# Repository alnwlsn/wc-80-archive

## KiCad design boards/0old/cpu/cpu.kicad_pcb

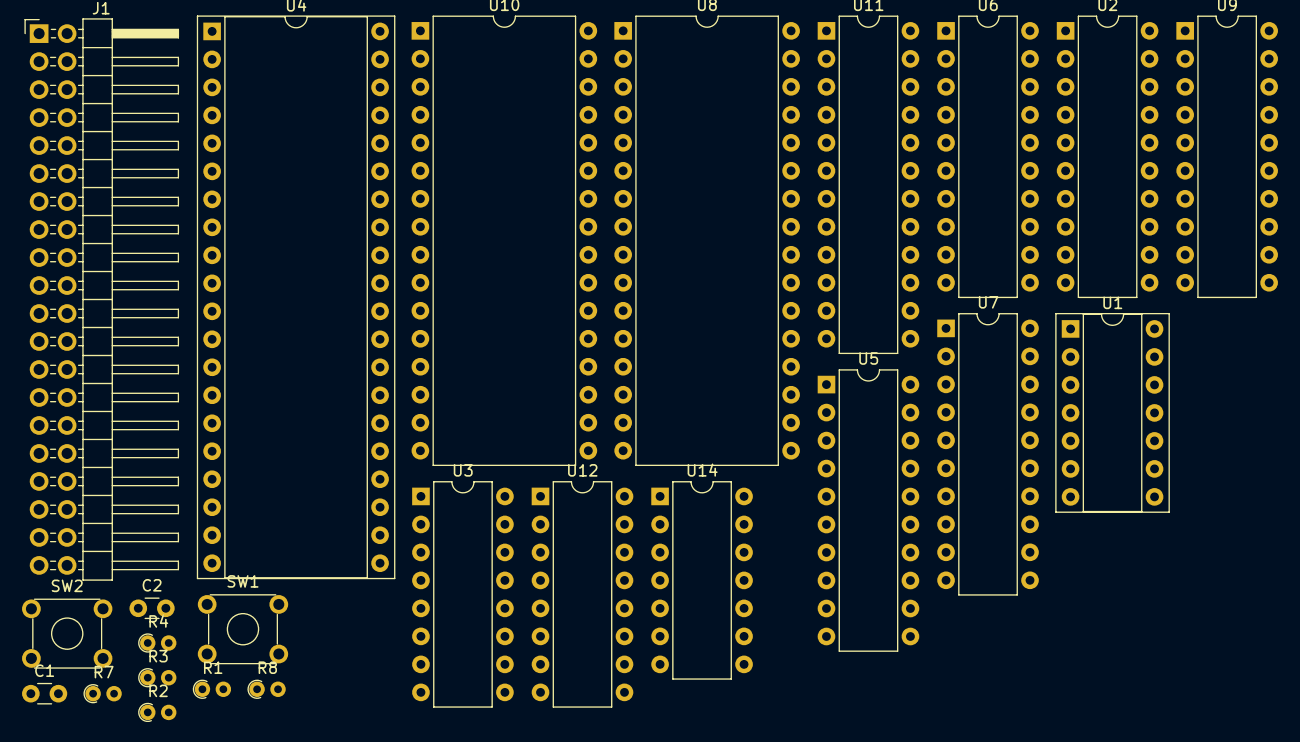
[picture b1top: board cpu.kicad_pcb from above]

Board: 2 copper layers, 24 parts (0 on the bottom side), 87 nets, no tracks yet.

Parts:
C1, C2: 1uF; C_Disc_D3.0mm_W1.6mm_P2.50mm
J1: Z80-BUS; PinHeader_2x20_P2.54mm_Horizontal
R1, R3: 100; R_Axial_DIN0204_L3.6mm_D1.6mm_P1.90mm_Vertical
R2, R4: 4k7; R_Axial_DIN0204_L3.6mm_D1.6mm_P1.90mm_Vertical
R7, R8: 330; R_Axial_DIN0204_L3.6mm_D1.6mm_P1.90mm_Vertical
SW1: RESET; SW_TH_Tactile_Omron_B3F-10xx
SW2: NMI; SW_TH_Tactile_Omron_B3F-10xx
U1: SN74HCT32N; DIP-14_W7.62mm_Socket
U2: SN74HCT244N; DIP-20_W7.62mm
U3, U12: 74LS670N; DIP-16_W7.62mm
U4: Z80CPU; DIP-40_W15.24mm_Socket
U5, U6: SN74HCT32N; DIP-20_W7.62mm
U7: 74HCT245N; DIP-20_W7.62mm
U8: 628128_DIP32_SSOP32; DIP-32_W15.24mm
U9: 74HCT273; DIP-20_W7.62mm
U10: SST39SF040; DIP-32_W15.24mm
U11: GAL22V10; DIP-24_W7.62mm
U14: 74LS132N; DIP-14_W7.62mm

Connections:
*CPUMEM: J1.10, U9.19
*EXTMEM: J1.9, U11.13
+5V: J1.1, J1.3, R2.2, R4.2, U1.14, U2.20, U4.11, U5.20, U6.20, U7.20, U8.30, U8.32, U9.20, U10.31, U10.32, U11.24
/ramAltHigh: U9.16, U11.15
/ramAltLow: U9.15, U11.16
/~rom~ram: U9.12, U11.14
BIOL: U9.11, U11.23
GND: C1.2, C2.2, J1.2, J1.4, SW1.1, SW2.1, U1.7, U2.10, U2.19, U4.29, U5.10, U6.10, U7.10, U8.16, U9.10, U10.16, U11.12
unnamed: C1.1, R1.1, R2.1, U14.1, U14.2
unnamed: C2.1, R3.1, R4.1, U14.4, U14.5
unnamed: R1.2, SW1.2
unnamed: R3.2, SW2.2
unnamed: R7.2, U14.3
unnamed: R8.2, U14.6
unnamed: U1.1, U1.13, U4.19
unnamed: U1.2, U1.5, U4.21, U7.1
unnamed: U1.3, U2.2
unnamed: U1.4, U1.9, U4.20
unnamed: U1.6, U2.6
unnamed: U1.8, U2.8
unnamed: U1.10, U1.12, U4.22
unnamed: U1.11, U2.4
unnamed: U2.1, U5.1, U5.19, U6.1, U6.19, U7.19
unnamed: U2.7, U4.24
unnamed: U2.9, U4.16
unnamed: U4.1, U6.8
unnamed: U4.2, U6.11
unnamed: U4.3, U6.13
unnamed: U4.4, U6.15
unnamed: U4.5, U6.17
unnamed: U4.7, U7.6
unnamed: U4.8, U7.5
unnamed: U4.9, U7.7
unnamed: U4.10, U7.8
unnamed: U4.12, U7.4
unnamed: U4.13, U7.9
unnamed: U4.14, U7.2
unnamed: U4.15, U7.3
unnamed: U4.30, U5.2
unnamed: U4.31, U5.4
unnamed: U4.32, U5.6
unnamed: U4.33, U5.8
unnamed: U4.34, U5.11
unnamed: U4.35, U5.13
unnamed: U4.36, U5.15
unnamed: U4.37, U5.17
unnamed: U4.38, U6.2
unnamed: U4.39, U6.4
unnamed: U4.40, U6.6
unnamed: U9.9, U10.1
unnamed: U9.5, U10.2
unnamed: U9.2, U10.3
unnamed: U9.6, U10.30
RAMA15: U8.31, U11.18
RAMA16: U8.2, U11.19
ZA0: J1.19, U8.12, U10.12, U11.9
ZA1: J1.20, U8.11, U10.11, U11.8
ZA2: J1.21, U8.10, U10.10, U11.7
ZA3: J1.22, U8.9, U10.9, U11.6
ZA4: J1.23, U8.8, U10.8, U11.5
ZA5: J1.24, U8.7, U10.7, U11.4
ZA6: J1.25, U8.6, U10.6, U11.3
ZA7: J1.26, U8.5, U10.5, U11.2
ZA8: J1.27, U8.27, U10.27
ZA9: J1.28, U8.26, U10.26
ZA10: J1.29, U8.23, U10.23
ZA11: J1.30, U8.25, U10.25
ZA12: J1.31, U8.4, U10.4
ZA13: J1.32, U8.28, U10.28
ZA14: J1.33, U8.3, U10.29
ZA15: J1.34, U11.17
ZD0: J1.11, U8.13, U9.3, U10.13
ZD1: J1.12, U8.14, U9.4, U10.14
ZD2: J1.13, U8.15, U9.7, U10.15
ZD3: J1.14, U8.17, U9.8, U10.17
ZD4: J1.15, U8.18, U9.13, U10.18
ZD5: J1.16, U8.19, U9.14, U10.19
ZD6: J1.17, U8.20, U9.17, U10.20
ZD7: J1.18, U8.21, U9.18, U10.21
ZIORQ: J1.6, U11.11
ZMREQ: J1.5, U11.1
ZNMI: J1.35, U4.17
ZRD: J1.7, U8.24, U10.24
ZRESET: J1.40, U4.26, U9.1
ZWR: J1.8, U8.29, U11.10
\RAMCS: U8.22, U11.21
\ROMCS: U10.22, U11.20

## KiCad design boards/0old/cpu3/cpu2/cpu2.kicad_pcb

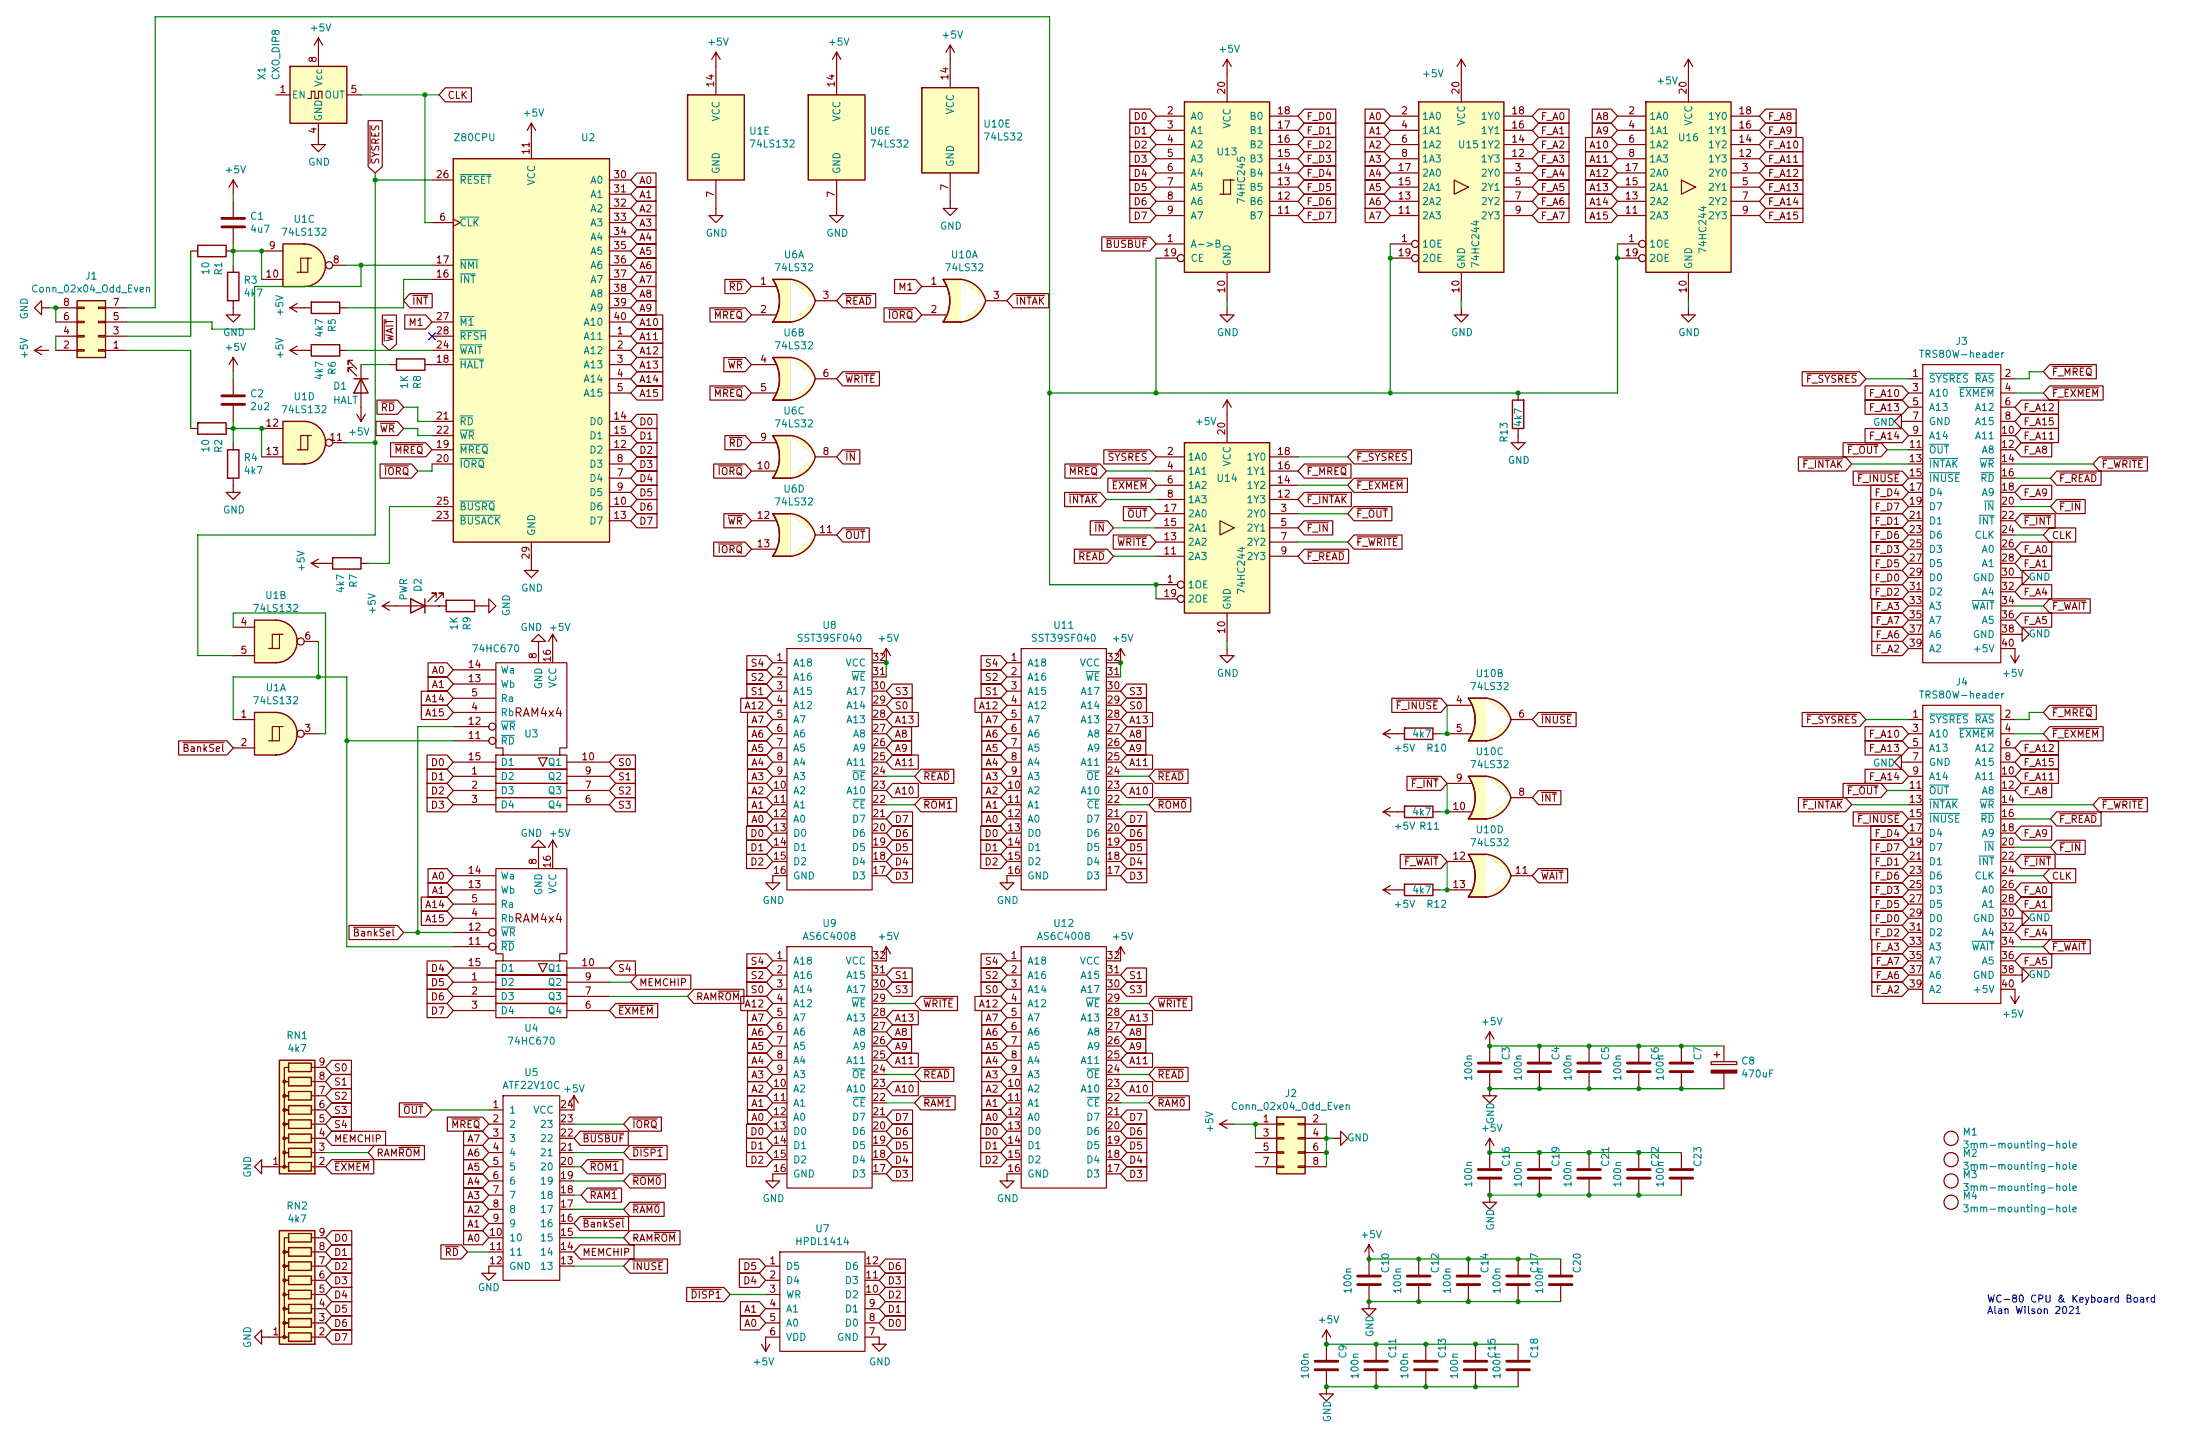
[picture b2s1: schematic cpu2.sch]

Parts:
C1: 4u7; C_0805_2012Metric
C2: 2u2; C_0805_2012Metric
C3, C4, C5, C6, C7, C9, C10, C11, C12, C13, C14, C15, C16, C17, C18, C19, C20, C21, C22, C23: 100n; C_0805_2012Metric
C8: 470uF; CP_Radial_D8.0mm_P3.50mm
D1: HALT; LED_D3.0mm_FlatTop
D2: PWR; LED_D3.0mm_FlatTop
J1, J2: Conn_02x04_Odd_Even; PinHeader_2x04_P2.54mm_Vertical
J3, J4: TRS80W-header; PinHeader_2x20_P2.54mm_Vertical
M1, M2, M3, M4: 3mm-mounting-hole; MountingHole_3.2mm_M3_DIN965_Pad
R1, R2: 10; R_0805_2012Metric
R3, R4, R5, R6, R7, R10, R11, R12, R13: 4k7; R_0805_2012Metric
R8, R9: 1K; R_0805_2012Metric
RN1, RN2: 4k7; R_Array_SIP9
U1: 74LS132; DIP-14_W7.62mm_Socket
U2: Z80CPU; DIP-40_W15.24mm_Socket
U3, U4: 74HC670; DIP-16_W7.62mm_Socket
U5: ATF22V10C; DIP-24_W7.62mm_Socket
U6, U10: 74LS32; DIP-14_W7.62mm_Socket
U7: HPDL1414; DIP-24_W15.24mm_Socket
U8, U11: SST39SF040; DIP-32_W15.24mm_Socket
U9, U12: AS6C4008; DIP-32_W15.24mm_Socket
U13: 74HC245; DIP-20_W7.62mm_Socket
U14, U15, U16: 74HC244; DIP-20_W7.62mm_Socket
X1: CXO_DIP8; Oscillator_DIP-8

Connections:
+5V: C1.1, C2.1, C3.1, C4.1, C5.1, C6.1, C7.1, C8.1, C9.1, C10.1, C11.1, C12.1, C13.1, C14.1, C15.1, C16.1, C17.1, C18.1, C19.1, C20.1, C21.1, C22.1, C23.1, D1.2 (A), D2.2 (A), J2.1, J2.3, J3.40 (+5V), J4.40 (+5V), R5.2, R6.2, R7.2, R10.2, R11.2, R12.2, U1.14 (VCC), U2.11 (VCC), U3.16 (VCC), U4.16 (VCC), U5.24 (VCC), U6.14 (VCC), U7.6 (VDD), U8.31 (~WE~), U8.32 (VCC), U9.32 (VCC), U10.14 (VCC), U11.31 (~WE~), U11.32 (VCC), U12.32 (VCC), U13.20 (VCC), U14.20 (VCC), U15.20 (VCC), U16.20 (VCC), X1.8 (Vcc)
A0: U2.30 (A0), U3.14 (Wa), U4.14 (Wa), U5.10, U7.5 (A0), U8.12 (A0), U9.12 (A0), U11.12 (A0), U12.12 (A0), U15.2 (1A0)
A1: U2.31 (A1), U3.13 (Wb), U4.13 (Wb), U5.9, U7.4 (A1), U8.11 (A1), U9.11 (A1), U11.11 (A1), U12.11 (A1), U15.4 (1A1)
A2: U2.32 (A2), U5.8, U8.10 (A2), U9.10 (A2), U11.10 (A2), U12.10 (A2), U15.6 (1A2)
A3: U2.33 (A3), U5.7, U8.9 (A3), U9.9 (A3), U11.9 (A3), U12.9 (A3), U15.8 (1A3)
A4: U2.34 (A4), U5.6, U8.8 (A4), U9.8 (A4), U11.8 (A4), U12.8 (A4), U15.17 (2A0)
A5: U2.35 (A5), U5.5, U8.7 (A5), U9.7 (A5), U11.7 (A5), U12.7 (A5), U15.15 (2A1)
A6: U2.36 (A6), U5.4, U8.6 (A6), U9.6 (A6), U11.6 (A6), U12.6 (A6), U15.13 (2A2)
A7: U2.37 (A7), U5.3, U8.5 (A7), U9.5 (A7), U11.5 (A7), U12.5 (A7), U15.11 (2A3)
A8: U2.38 (A8), U8.27 (A8), U9.27 (A8), U11.27 (A8), U12.27 (A8), U16.2 (1A0)
A9: U2.39 (A9), U8.26 (A9), U9.26 (A9), U11.26 (A9), U12.26 (A9), U16.4 (1A1)
A10: U2.40 (A10), U8.23 (A10), U9.23 (A10), U11.23 (A10), U12.23 (A10), U16.6 (1A2)
A11: U2.1 (A11), U8.25 (A11), U9.25 (A11), U11.25 (A11), U12.25 (A11), U16.8 (1A3)
A12: U2.2 (A12), U8.4 (A12), U9.4 (A12), U11.4 (A12), U12.4 (A12), U16.17 (2A0)
A13: U2.3 (A13), U8.28 (A13), U9.28 (A13), U11.28 (A13), U12.28 (A13), U16.15 (2A1)
A14: U2.4 (A14), U3.5 (Ra), U4.5 (Ra), U16.13 (2A2)
A15: U2.5 (A15), U3.4 (Rb), U4.4 (Rb), U16.11 (2A3)
CLK: J3.24 (CLK), J4.24 (CLK), U2.6 (~CLK~), X1.5 (OUT)
D0: RN2.9 (R8), U2.14 (D0), U3.15 (D1), U7.8 (D0), U8.13 (D0), U9.13 (D0), U11.13 (D0), U12.13 (D0), U13.2 (A0)
D1: RN2.8 (R7), U2.15 (D1), U3.1 (D2), U7.9 (D1), U8.14 (D1), U9.14 (D1), U11.14 (D1), U12.14 (D1), U13.3 (A1)
D2: RN2.7 (R6), U2.12 (D2), U3.2 (D3), U7.10 (D2), U8.15 (D2), U9.15 (D2), U11.15 (D2), U12.15 (D2), U13.4 (A2)
D3: RN2.6 (R5), U2.8 (D3), U3.3 (D4), U7.11 (D3), U8.17 (D3), U9.17 (D3), U11.17 (D3), U12.17 (D3), U13.5 (A3)
D4: RN2.5 (R4), U2.7 (D4), U4.15 (D1), U7.2 (D4), U8.18 (D4), U9.18 (D4), U11.18 (D4), U12.18 (D4), U13.6 (A4)
D5: RN2.4 (R3), U2.9 (D5), U4.1 (D2), U7.1 (D5), U8.19 (D5), U9.19 (D5), U11.19 (D5), U12.19 (D5), U13.7 (A5)
D6: RN2.3 (R2), U2.10 (D6), U4.2 (D3), U7.12 (D6), U8.20 (D6), U9.20 (D6), U11.20 (D6), U12.20 (D6), U13.8 (A6)
D7: RN2.2 (R1), U2.13 (D7), U4.3 (D4), U8.21 (D7), U9.21 (D7), U11.21 (D7), U12.21 (D7), U13.9 (A7)
F_A0: J3.26 (A0), J4.26 (A0), U15.18 (1Y0)
F_A1: J3.28 (A1), J4.28 (A1), U15.16 (1Y1)
F_A2: J3.39 (A2), J4.39 (A2), U15.14 (1Y2)
F_A3: J3.33 (A3), J4.33 (A3), U15.12 (1Y3)
F_A4: J3.32 (A4), J4.32 (A4), U15.3 (2Y0)
F_A5: J3.36 (A5), J4.36 (A5), U15.5 (2Y1)
F_A6: J3.37 (A6), J4.37 (A6), U15.7 (2Y2)
F_A7: J3.35 (A7), J4.35 (A7), U15.9 (2Y3)
F_A8: J3.12 (A8), J4.12 (A8), U16.18 (1Y0)
F_A9: J3.18 (A9), J4.18 (A9), U16.16 (1Y1)
F_A10: J3.3 (A10), J4.3 (A10), U16.14 (1Y2)
F_A11: J3.10 (A11), J4.10 (A11), U16.12 (1Y3)
F_A12: J3.6 (A12), J4.6 (A12), U16.3 (2Y0)
F_A13: J3.5 (A13), J4.5 (A13), U16.5 (2Y1)
F_A14: J3.9 (A14), J4.9 (A14), U16.7 (2Y2)
F_A15: J3.8 (A15), J4.8 (A15), U16.9 (2Y3)
F_D0: J3.29 (D0), J4.29 (D0), U13.18 (B0)
F_D1: J3.21 (D1), J4.21 (D1), U13.17 (B1)
F_D2: J3.31 (D2), J4.31 (D2), U13.16 (B2)
F_D3: J3.25 (D3), J4.25 (D3), U13.15 (B3)
F_D4: J3.17 (D4), J4.17 (D4), U13.14 (B4)
F_D5: J3.27 (D5), J4.27 (D5), U13.13 (B5)
F_D6: J3.23 (D6), J4.23 (D6), U13.12 (B6)
F_D7: J3.19 (D7), J4.19 (D7), U13.11 (B7)
GND: C3.2, C4.2, C5.2, C6.2, C7.2, C8.2, C9.2, C10.2, C11.2, C12.2, C13.2, C14.2, C15.2, C16.2, C17.2, C18.2, C19.2, C20.2, C21.2, C22.2, C23.2, J1.6, J1.8, J2.2, J2.4, J2.6, J2.8, J3.7 (GND), J3.30 (GND), J3.38 (GND), J4.7 (GND), J4.30 (GND), J4.38 (GND), R3.2, R4.2, R9.1, R13.1, RN1.1 (common), RN2.1 (common), U1.7 (GND), U2.29 (GND), U3.8 (GND), U4.8 (GND), U5.12 (GND), U6.7 (GND), U7.7 (GND), U8.16 (GND), U9.16 (GND), U10.7 (GND), U11.16 (GND), U12.16 (GND), U13.10 (GND), U14.10 (GND), U15.10 (GND), U16.10 (GND), X1.4 (GND)
M1: U2.27 (~M1~), U10.1
MEMCHIP: RN1.4 (R3), U4.9 (Q2), U5.14
unnamed: C1.2, R1.1, R3.1, U1.9, U1.10
unnamed: C2.2, R2.1, R4.1, U1.12, U1.13
unnamed: D1.1 (K), R8.2
unnamed: D2.1 (K), R9.2
unnamed: J1.1, R2.2
unnamed: J1.2, J1.4
unnamed: J1.3, R1.2
unnamed: J1.5, U1.8, U2.17 (~NMI~)
unnamed: J1.7, R13.2, U13.19 (CE), U14.1 (1OE), U14.19 (2OE), U15.1 (1OE), U15.19 (2OE), U16.1 (1OE), U16.19 (2OE)
unnamed: R7.1, U2.25 (~BUSRQ~)
unnamed: R8.1, U2.18 (~HALT~)
unnamed: U1.1, U1.6, U3.11 (~RD), U4.11 (~RD)
unnamed: U1.3, U1.4
RAM~ROM~: RN1.3 (R2), U4.7 (Q3), U5.15
S0: RN1.9 (R8), U3.10 (Q1), U8.29 (A14), U9.3 (A14), U11.29 (A14), U12.3 (A14)
S1: RN1.8 (R7), U3.9 (Q2), U8.3 (A15), U9.31 (A15), U11.3 (A15), U12.31 (A15)
S2: RN1.7 (R6), U3.7 (Q3), U8.2 (A16), U9.2 (A16), U11.2 (A16), U12.2 (A16)
S3: RN1.6 (R5), U3.6 (Q4), U8.30 (A17), U9.30 (A17), U11.30 (A17), U12.30 (A17)
S4: RN1.5 (R4), U4.10 (Q1), U8.1 (A18), U9.1 (A18), U11.1 (A18), U12.1 (A18)
~BUSBUF~: U5.22, U13.1 (A->B)
~BankSel~: U1.2, U3.12 (~WR), U4.12 (~WR), U5.16
~DISP1~: U5.21, U7.3 (WR)
~EXMEM~: RN1.2 (R1), U4.6 (Q4), U14.6 (1A2)
~F_EXMEM~: J3.4 (~EXMEM~), J4.4 (~EXMEM~), U14.14 (1Y2)
~F_INTAK~: J3.13 (~INTAK~), J4.13 (~INTAK~), U14.12 (1Y3)
~F_INT~: J3.22 (~INT~), J4.22 (~INT~), R11.1, U10.9, U10.10
~F_INUSE~: J3.15 (~INUSE~), J4.15 (~INUSE~), R10.1, U10.4, U10.5
~F_IN~: J3.20 (~IN~), J4.20 (~IN~), U14.5 (2Y1)
~F_MREQ~: J3.2 (~RAS~), J4.2 (~RAS~), U14.16 (1Y1)
~F_OUT~: J3.11 (~OUT~), J4.11 (~OUT~), U14.3 (2Y0)
~F_READ~: J3.16 (~RD~), J4.16 (~RD~), U14.9 (2Y3)
~F_SYSRES~: J3.1 (~SYSRES~), J4.1 (~SYSRES~), U14.18 (1Y0)
~F_WAIT~: J3.34 (~WAIT~), J4.34 (~WAIT~), R12.1, U10.12, U10.13
~F_WRITE~: J3.14 (~WR~), J4.14 (~WR~), U14.7 (2Y2)
~INTAK~: U10.3, U14.8 (1A3)
~INT~: R5.1, U2.16 (~INT~), U10.8
~INUSE~: U5.13, U10.6
~IN~: U6.8, U14.15 (2A1)
~IORQ~: U2.20 (~IORQ~), U5.23, U6.10, U6.13, U10.2
~MREQ~: U2.19 (~MREQ~), U5.2, U6.2, U6.5, U14.4 (1A1)
~OUT~: U5.1, U6.11, U14.17 (2A0)
~RAM0~: U5.17, U12.22 (~CE~)
~RAM1~: U5.18, U9.22 (~CE~)
~RD~: U2.21 (~RD~), U5.11, U6.1, U6.9
~READ~: U6.3, U8.24 (~OE~), U9.24 (~OE~), U11.24 (~OE~), U12.24 (~OE~), U14.11 (2A3)
~ROM0~: U5.19, U11.22 (~CE~)
~ROM1~: U5.20, U8.22 (~CE~)
~SYSRES~: U1.5, U1.11, U2.26 (~RESET~), U14.2 (1A0)
~WAIT~: R6.1, U2.24 (~WAIT~), U10.11
~WRITE~: U6.6, U9.29 (~WE~), U12.29 (~WE~), U14.13 (2A2)
~WR~: U2.22 (~WR~), U6.4, U6.12

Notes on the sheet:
WC-80 CPU & Keyboard Board Alan Wilson 2021

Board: 2 copper layers, 65 parts (33 on the bottom side), 104 nets, no tracks yet.

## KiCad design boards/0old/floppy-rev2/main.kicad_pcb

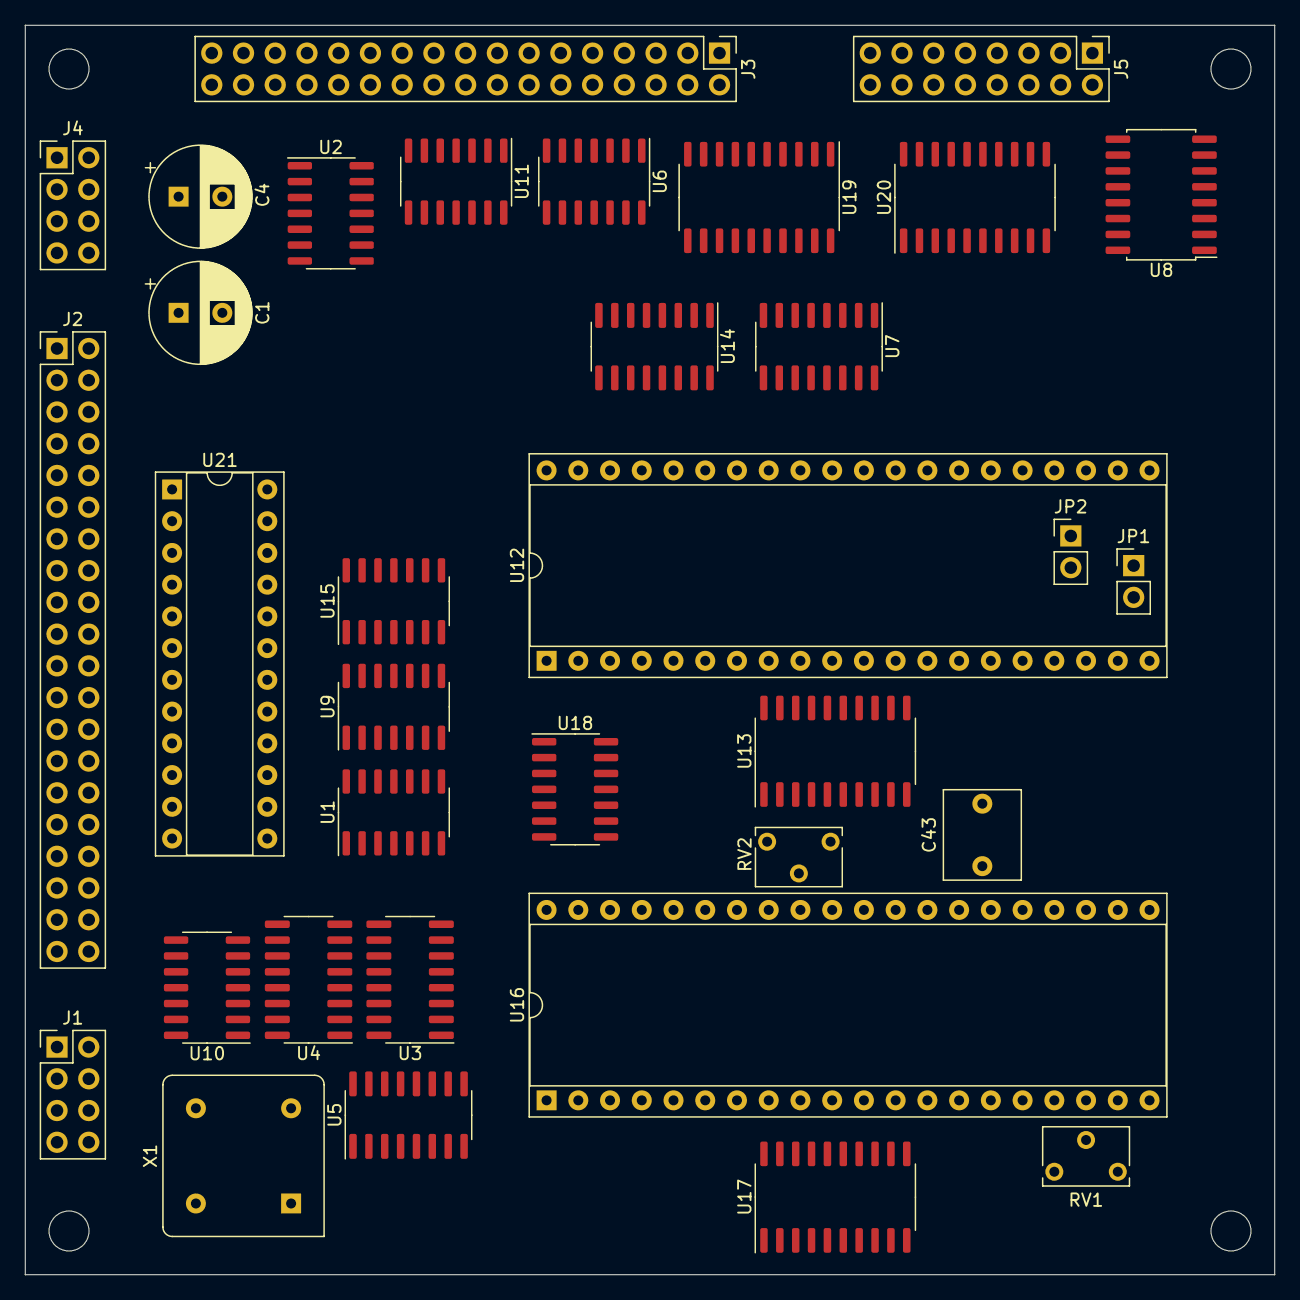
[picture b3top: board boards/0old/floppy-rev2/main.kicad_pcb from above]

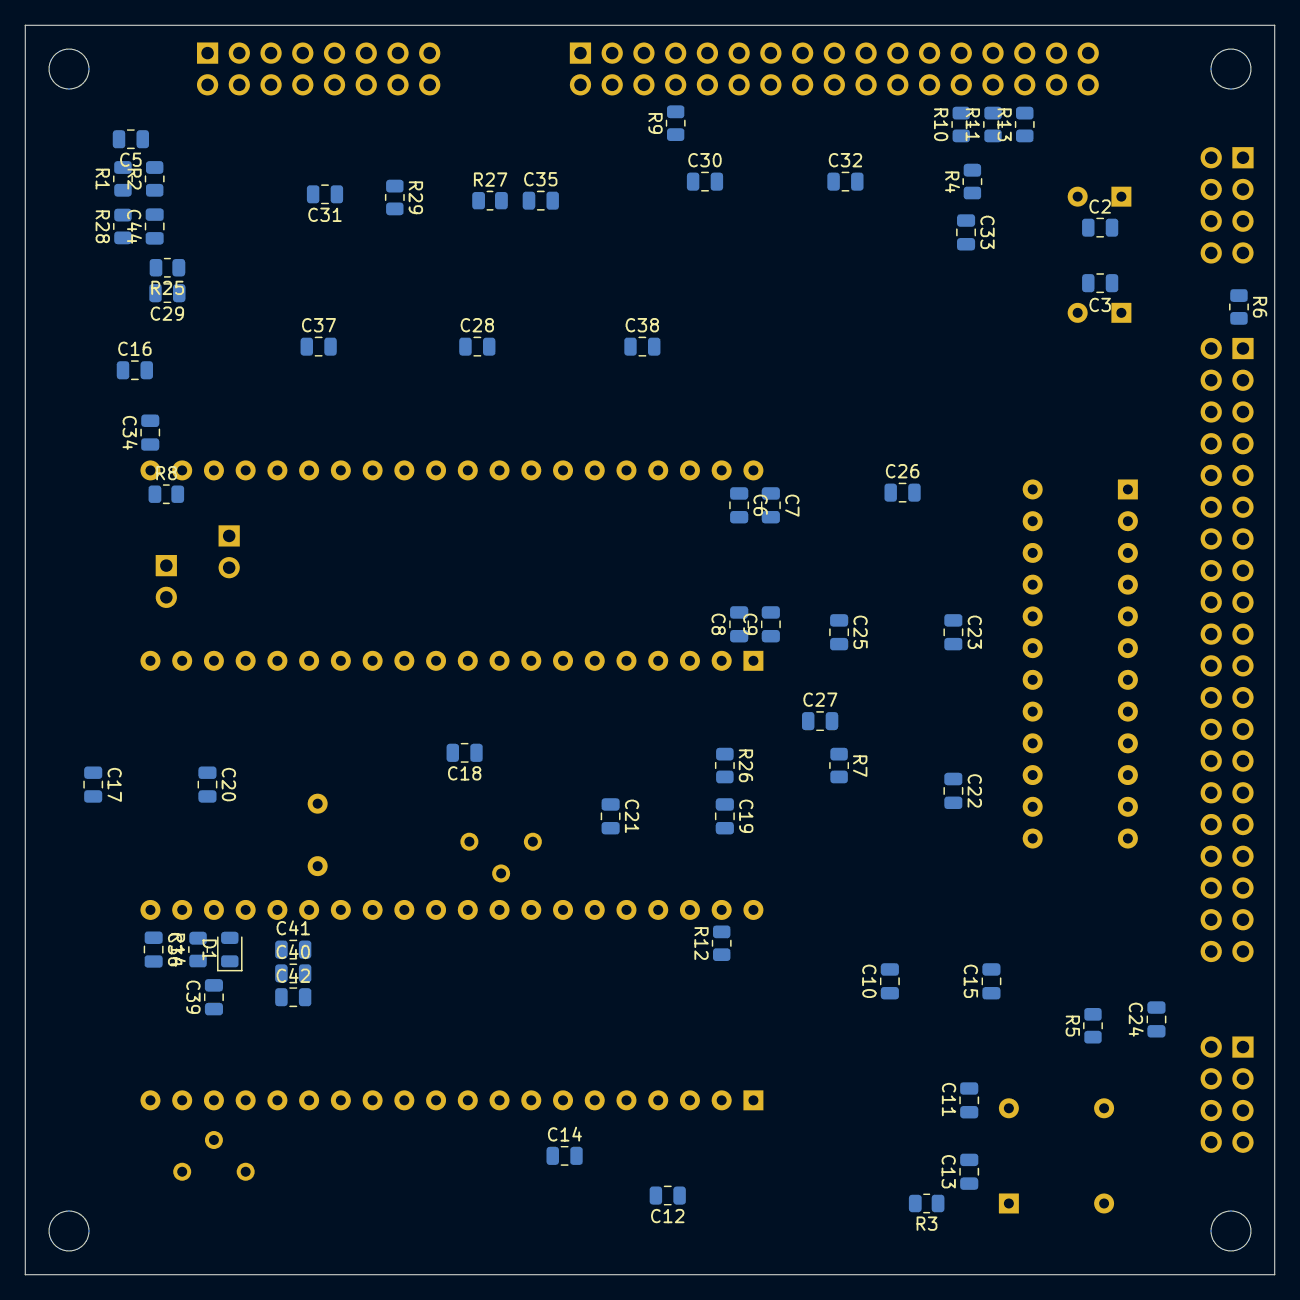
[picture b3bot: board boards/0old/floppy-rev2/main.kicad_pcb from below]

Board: 2 copper layers, 100.0 x 100.0 mm, 99 parts (61 on the bottom side), 134 nets, no tracks yet.

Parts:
C1, C4: 470uF; CP_Radial_D8.0mm_P3.50mm
C2, C3, C6, C7, C8, C9, C10, C11, C12, C13, C14, C15, C16, C17, C18, C19, C20, C21, C22, C23, C24, C25, C26, C27, C28, C29, C30, C31, C32, C33, C34, C35, C36, C37, C38: 100n; C_0805_2012Metric
C5: 33uF; C_0805_2012Metric
C39: 150nF; C_0805_2012Metric
C40, C41, C42: 15pF; C_0805_2012Metric
C43: 60pF; C_Rect_L7.0mm_W6.0mm_P5.00mm
C44: 200p; C_0805_2012Metric
D1: DIODE; D_0805_2012Metric
J1, J4: Conn_02x04_Odd_Even; PinHeader_2x04_P2.54mm_Vertical
J2: TRS80W-header; PinHeader_2x20_P2.54mm_Vertical
J3: Floppy-header; PinHeader_2x17_P2.54mm_Vertical
J5: Conn_01x16_Male; PinHeader_2x08_P2.54mm_Vertical
JP1: SIDE; PinHeader_1x02_P2.54mm_Vertical
JP2: TEST; PinHeader_1x02_P2.54mm_Vertical
M1, M2, M3, M4: 3mm-mounting-hole; MountingHole_3.2mm_M3_DIN965
R1: 200K; R_0805_2012Metric
R2, R28, R29: 4K7; R_0805_2012Metric
R3, R4, R5, R6, R7, R8, R12, R26, R27: 10K; R_0805_2012Metric
R9, R10, R11, R13: 150; R_0805_2012Metric
R14: 1K; R_0805_2012Metric
R25: 20K; R_0805_2012Metric
RV1: 50K; Potentiometer_Bourns_3266W_Vertical
RV2: 10K; Potentiometer_Bourns_3266W_Vertical
U1, U2: 74LS32; SOIC-14_3.9x8.7mm_P1.27mm
U3, U4, U5: 4518; SOP-16_3.9x9.9mm_P1.27mm
U6, U11: 74LS06; SOIC-14_3.9x8.7mm_P1.27mm
U7: 74LS175; SOP-16_3.9x9.9mm_P1.27mm
U8: 74LS123; SO-16_5.3x10.2mm_P1.27mm
U9, U10, U18: 74LS74; SOIC-14_3.9x8.7mm_P1.27mm
U12: WD1771; DIP-40_W15.24mm_Socket
U13: 74LS640; SO-20_5.3x12.6mm_P1.27mm
U14: 74LS157; SOP-16_3.9x9.9mm_P1.27mm
U15: 74LS02; SOIC-14_3.9x8.7mm_P1.27mm
U16: WD2793; DIP-40_W15.24mm_Socket
U17: 74LS245; SO-20_5.3x12.6mm_P1.27mm
U19: 74LS244; SO-20_5.3x12.6mm_P1.27mm
U20: 74LS273; SO-20_5.3x12.6mm_P1.27mm
U21: ATF22V10C; DIP-24_W7.62mm_Socket
X1: CXO_DIP8; Oscillator_DIP-8

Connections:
1MHz: U9.9, U12.24
2MHz: U5.3, U9.11, U16.24
4MHz: U5.2, X1.5
40Hz: U4.6, U4.10, U10.3
+5V: C1.1, C2.1, C3.1, C4.1, C10.1, C11.1, C12.1, C13.1, C14.1, C15.1, C16.1, C17.1, C18.1, C19.1, C20.1, C21.1, C22.1, C23.1, C24.1, C25.1, C26.1, C27.1, C28.1, C29.1, C30.1, C31.1, C32.1, C33.1, C34.1, C35.1, C36.1, C37.1, C38.1, J2.40, J4.1, J4.3, R1.1, R2.1, R3.1, R4.1, R5.1, R6.1, R7.1, R8.1, R9.1, R10.1, R11.1, R12.1, R13.1, R25.1, R26.1, R27.1, R28.1, R29.1, RV1.1, RV2.3, U1.14, U2.14, U3.16, U4.16, U5.16, U6.14, U7.16, U8.16, U9.14, U10.14, U11.14, U12.21, U13.20, U14.16, U15.14, U16.21, U17.20, U19.20, U20.20, U21.24, X1.8
+12V: C6.1, C7.1, J4.7, U12.40
-5V: C8.1, C9.1, J4.5, U12.1
D0: U1.4, U6.9, U7.2
D1: U1.5, U6.3, U7.7
D2: U1.9, U6.5, U7.10
D3: U1.10, U6.1, U7.15
DFL: U7.9, U8.9, U21.16
F_A0: J2.26, U12.5, U16.5, U21.5
F_A1: J2.28, U12.6, U16.6, U21.6
F_A2: J2.39, U21.7
F_A3: J2.33, U21.8
F_A4: J2.32, U21.9
F_D0: J2.29, U7.4, U13.2, U17.2, U18.2, U20.18
F_D1: J2.21, U7.5, U13.3, U17.3, U20.17
F_D2: J2.31, U7.12, U13.4, U17.4, U20.14
F_D3: J2.25, U7.13, U13.5, U17.5, U20.13
F_D4: J2.17, U13.6, U17.6, U19.17, U20.8
F_D5: J2.27, U13.7, U17.7, U19.15, U20.7
F_D6: J2.23, U13.8, U17.8, U19.13, U19.14, U20.4
F_D7: J2.19, U13.9, U17.9, U19.11, U19.12, U20.3
GND: C1.2, C2.2, C3.2, C4.2, C5.2, C6.2, C7.2, C8.2, C9.2, C10.2, C11.2, C12.2, C13.2, C14.2, C15.2, C16.2, C17.2, C18.2, C19.2, C20.2, C21.2, C22.2, C23.2, C24.2, C25.2, C26.2, C27.2, C28.2, C29.2, C30.2, C31.2, C32.2, C33.2, C34.2, C35.2, C36.2, C37.2, C38.2, C39.1, C40.1, C41.1, C42.1, C43.2, C44.2, J2.7, J2.30, J2.38, J3.1, J3.3, J3.5, J3.7, J3.9, J3.11, J3.13, J3.15, J3.17, J3.19, J3.21, J3.23, J3.25, J3.27, J3.29, J3.31, J3.33, J4.2, J4.4, J4.6, J4.8, J5.1, J5.15, J5.16, JP2.2, RV1.3, RV2.1, U1.7, U2.7, U3.1, U3.7, U3.8, U3.9, U3.15, U4.1, U4.7, U4.8, U4.9, U4.15, U5.1, U5.7, U5.8, U5.9, U5.15, U6.7, U7.8, U8.1, U8.7, U8.8, U8.14, U9.7, U10.2, U10.7, U10.12, U11.7, U12.20, U13.10, U14.8, U14.15, U15.7, U16.20, U17.10, U19.10, U20.10, U21.12, X1.4
INTCLK: U10.9, U11.13, U19.8
INTFLOP: U1.3, U6.13, U19.6
MOTOR: U6.11, U7.1, U8.5
unnamed: C5.1, R1.2, U8.6
unnamed: C39.2, D1.1, R14.1
unnamed: C40.2, C41.2, C42.2, C43.1, U16.26
unnamed: C44.1, R25.2, U8.15
unnamed: D1.2, R14.2, U16.23
unnamed: J3.6, JP1.1, U6.2
unnamed: J3.8, R9.2, U2.4, U2.5
unnamed: J3.10, U6.8
unnamed: J3.12, U6.4
unnamed: J3.14, U6.6
unnamed: J3.16, U6.10
unnamed: J3.18, U11.2
unnamed: J3.20, U11.4
unnamed: J3.22, U11.8
unnamed: J3.24, U11.6
unnamed: J3.26, R10.2, U2.9, U2.10
unnamed: J3.28, R11.2, U2.12, U2.13
unnamed: J3.30, R13.2, U2.1, U2.2
unnamed: J5.2, U8.4
unnamed: J5.3, U20.19
unnamed: J5.4, U20.16
unnamed: J5.5, U19.3
unnamed: J5.6, U20.15
unnamed: J5.7, U20.12
unnamed: J5.8, U20.9
unnamed: J5.9, U20.6
unnamed: J5.10, U20.5
unnamed: J5.11, U20.2
unnamed: J5.12, U19.9
unnamed: J5.13, U19.7
unnamed: J5.14, U19.5
unnamed: JP2.1, U16.22
unnamed: R2.2, U8.10, U8.11
unnamed: R3.2, U9.10, U9.13
unnamed: R4.2, U1.2, U12.39
unnamed: R5.2, U10.1, U10.13
unnamed: R8.2, U12.18, U12.22, U12.25, U12.26, U12.33, U12.37
unnamed: R12.2, U1.1, U16.39
unnamed: R26.2, U18.1, U18.4
unnamed: R27.2, U19.2, U19.4
unnamed: R28.2, U8.3
unnamed: R29.2, U20.1
unnamed: RV1.2, U16.18
unnamed: RV2.2, U16.33
unnamed: U1.11, U12.23, U12.32, U16.32, U16.40
unnamed: U1.8, U1.12
unnamed: U1.6, U1.13
unnamed: U3.2, U5.14
unnamed: U3.6, U3.10
unnamed: U3.14, U4.2
unnamed: U5.6, U5.10
unnamed: U9.8, U9.12
unnamed: U10.5, U10.10
unnamed: U11.1, U14.9
unnamed: U11.3, U14.12
unnamed: U11.5, U14.7
unnamed: U11.9, U14.4
unnamed: U11.11, U21.23
unnamed: U12.2, U13.1, U16.2, U17.1
unnamed: U12.4, U16.4
unnamed: U12.7, U13.18
unnamed: U12.8, U13.17
unnamed: U12.9, U13.16
unnamed: U12.10, U13.15
unnamed: U12.11, U13.14
unnamed: U12.12, U13.13
unnamed: U12.13, U13.12
unnamed: U12.14, U13.11
unnamed: U12.15, U14.13
unnamed: U12.16, U14.10
unnamed: U12.27, U15.4
unnamed: U12.30, U14.6
unnamed: U12.31, U14.3
unnamed: U2.8, U12.34, U16.34
unnamed: U2.6, U12.35, U16.35
unnamed: U2.11, U12.36, U16.36
unnamed: U14.2, U16.31
unnamed: U14.5, U16.30
unnamed: U14.11, U16.16
unnamed: U14.14, U16.15
unnamed: U2.3, U15.5, U15.6, U16.27
unnamed: U15.9, U18.5
unnamed: U16.1, U16.29
unnamed: U16.7, U17.18
unnamed: U16.8, U17.17
unnamed: U16.9, U17.16
unnamed: U16.10, U17.15
unnamed: U16.11, U17.14
unnamed: U16.12, U17.13
unnamed: U16.13, U17.12
unnamed: U16.14, U17.11
unnamed: U16.17, U16.25
~37E0~: U10.4, U10.11, U19.1, U21.14
~1771~: U12.3, U13.19, U15.13
~2793~: R7.2, U14.1, U15.10, U15.11, U15.12, U16.3, U17.19
~F_EXMEM~: J2.4, U21.13
~F_INT~: J2.22, U6.12, U11.12
~F_INUSE~: J2.15, U11.10
~F_IN~: J2.20, U21.2
~F_OUT~: J2.11, U21.1
~F_READ~: J2.16, U21.4
~F_SYSRES~: J2.1, R6.2, U12.19, U16.19
~F_WRITE~: J2.14, U21.3
~PRINTREAD~: U19.19, U21.20
~PRINTWRITE~: U8.2, U20.11, U21.17
